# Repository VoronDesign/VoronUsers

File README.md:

# VoronUsers user mod repository

Welcome to VoronUsers. This is a place to share your mods for the VoronDesign 3D printers and find useful mods and resources from other Voron community members.

Check the [`printer_mods`](./printer_mods) folder for mods that apply to the current generation of printers. 

All mods that apply to older (=legacy) printers can be found in the [`legacy printers`](./legacy_printers) folder.

Mods where the authors have abandoned development can be found in the [`orphaned mods`](./orphaned_mods/) folder. If you want to start maintaining one of them, feel free to reach out via a [GitHub issue](https://github.com/VoronDesign/VoronUsers/issues/new/choose).

Looking to submit a mod? Check the [mod submission rules](https://github.com/VoronDesign/VoronUsers/wiki/Mod-Submission-Rules) and instructions on [how to submit to VoronUsers](https://github.com/VoronDesign/VoronUsers/wiki/How-to-Submit-to-VoronUsers)

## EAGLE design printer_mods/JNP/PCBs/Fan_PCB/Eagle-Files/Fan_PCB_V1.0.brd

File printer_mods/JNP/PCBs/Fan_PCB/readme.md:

Notes can be found in the schematic

Standard 2 layer PCB, 35µm (1oz) copper, TG-135, 1.6mm thickness, surface finish of your choice

Dimensions: 40x30mm

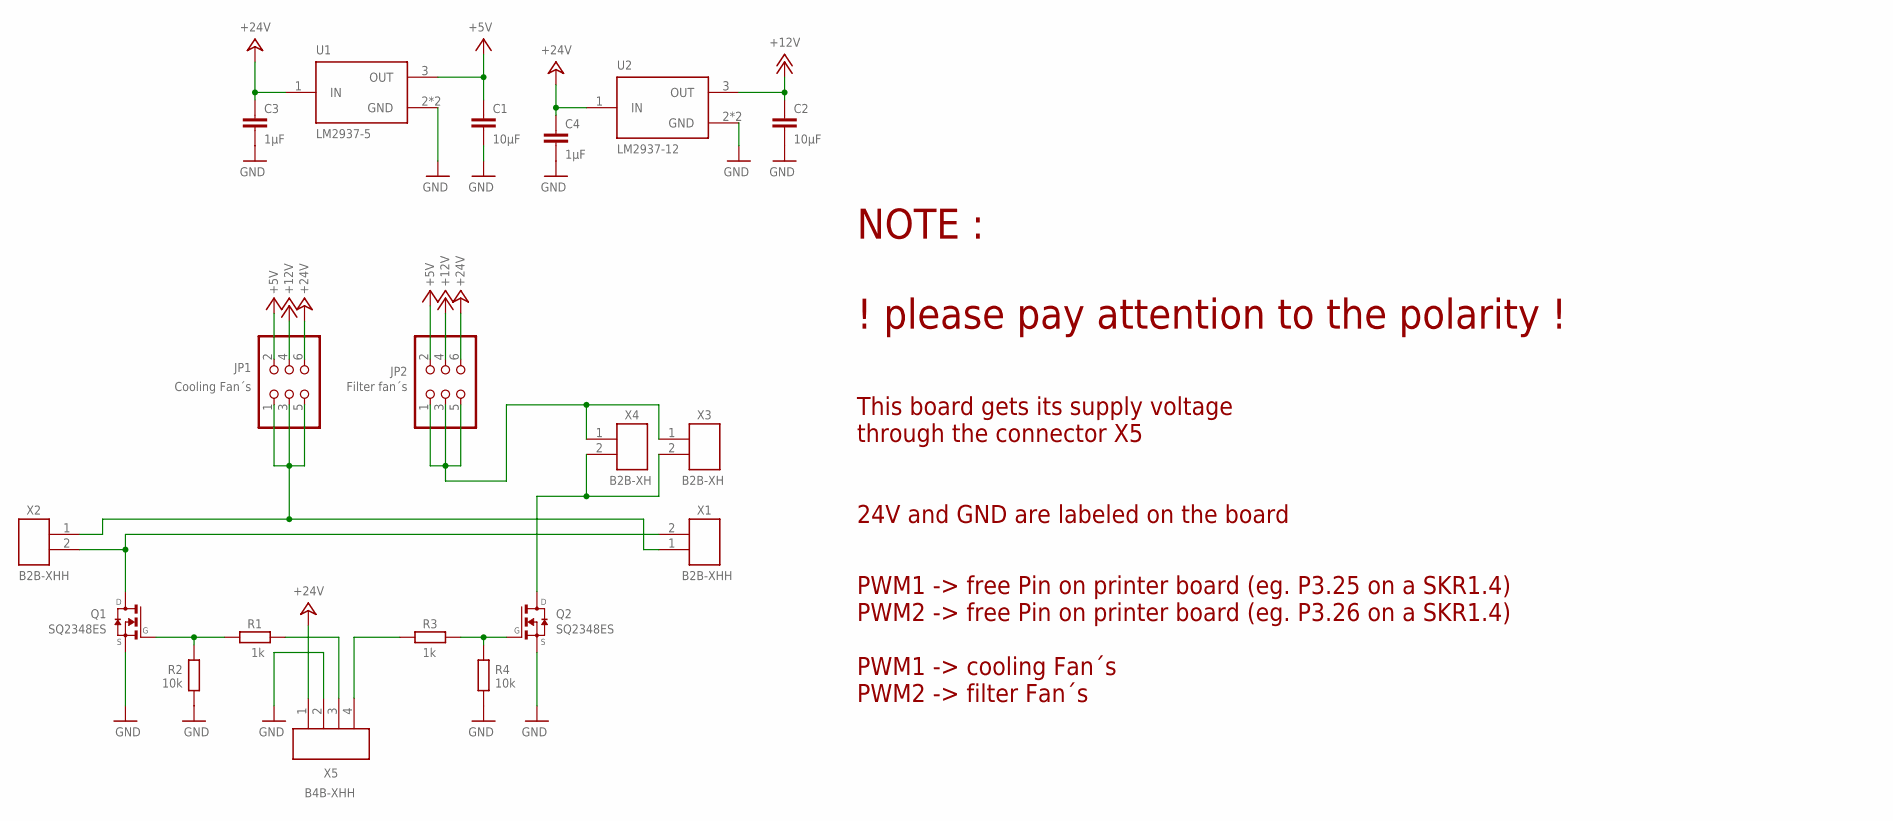
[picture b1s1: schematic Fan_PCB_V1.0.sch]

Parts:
C1, C2: 10µF; C1206
C3, C4: 1µF; C1206
JP1: Cooling Fan´s; 2X03
JP2: Filter fan´s; 2X03
Q1, Q2: SQ2348ES; TRANSISTOR-FET_SOT23
R1, R3: 1k; R0805
R2, R4: 10k; R0805
U1: LM2937-5; SOT-223-4
U2: LM2937-12; SOT-223-4
X1, X2: B2B-XHH; B2B-XH-H
X3, X4: B2B-XH; B2B-XH-A
X5: B4B-XHH; B4B-XH-H

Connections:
+5V: C1.1, JP1.2, JP2.2, U1.3 (OUT)
+12V: C2.1, JP1.4, JP2.4, U2.3 (OUT)
+24V: C3.1, C4.1, JP1.6, JP2.6, U1.1 (IN), U2.1 (IN), X5.1
GND: C1.2, C2.2, C3.2, C4.2, Q1.2 (S), Q2.2 (S), R2.1, R4.1, U1.2 (GND), U1.4 (GND), U2.2 (GND), U2.4 (GND), X5.2
unnamed: Q1.3 (D), X1.2, X2.2
unnamed: JP1.1, JP1.3, JP1.5, X1.1, X2.1
unnamed: Q2.3 (D), X3.2, X4.2
unnamed: JP2.1, JP2.3, JP2.5, X3.1, X4.1
unnamed: Q1.1 (G), R1.2, R2.2
unnamed: Q2.1 (G), R3.2, R4.2
unnamed: R1.1, X5.3
unnamed: R3.1, X5.4

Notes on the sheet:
PWM1 -> free Pin on printer board (eg. P3.25 on a SKR1.4) PWM2 -> free Pin on printer board (eg. P3.26 on a SKR1.4) PWM1 -> cooling Fan´s PWM2 -> filter Fan´s
This board gets its supply voltage through the connector X5 24V and GND are labeled on the board
NOTE : ! please pay attention to the polarity !

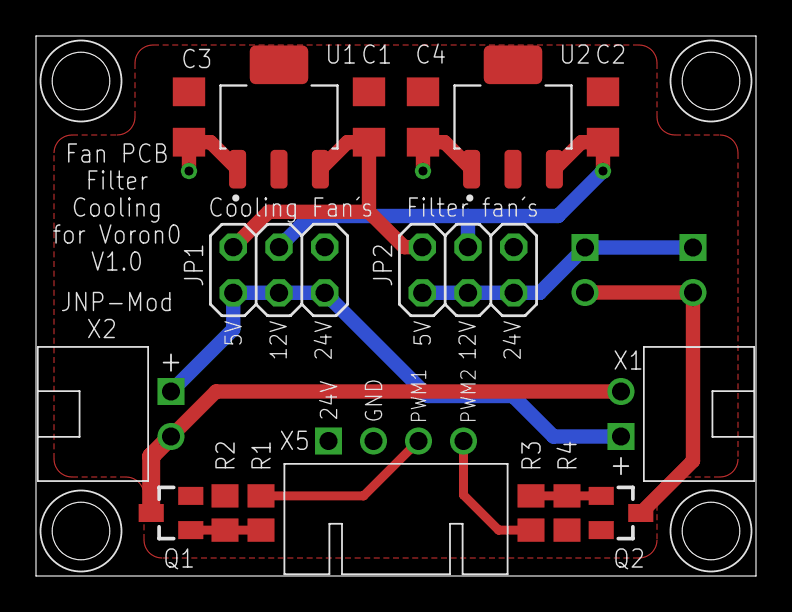
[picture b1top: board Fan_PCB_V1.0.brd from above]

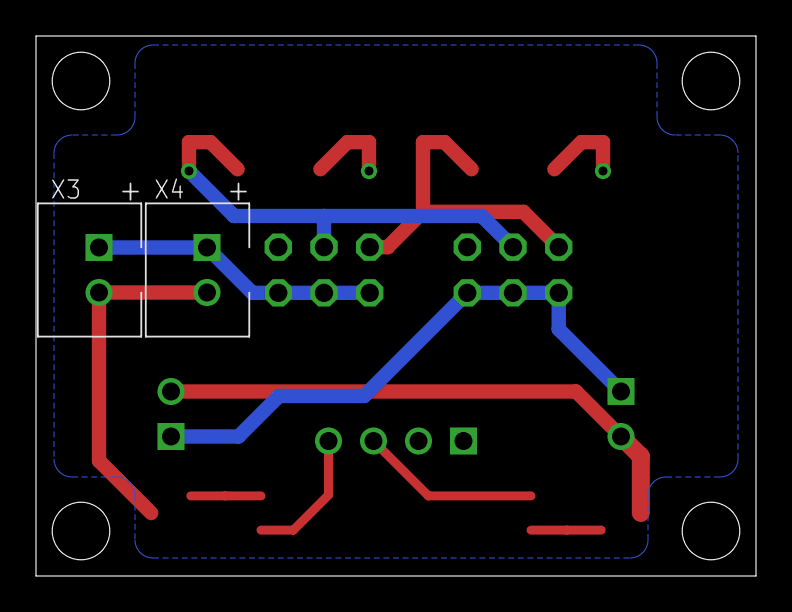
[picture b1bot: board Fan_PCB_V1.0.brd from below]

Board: 2 copper layers, 40.0 x 30.0 mm, 19 parts (2 on the bottom side), 12 nets.

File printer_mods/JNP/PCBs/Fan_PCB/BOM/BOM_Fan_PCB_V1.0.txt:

Qty Value         Device                  Package              Parts  Description                    
2   10k           RESISTOR			      0805                 R2, R4 RESISTOR    
2   10µF          CAPACITOR               1206                 C1, C2 CAPACITOR    
2   1k            RESISTOR				  0805                 R1, R3 RESISTOR  
2   1µF           CAPACITOR               1206                 C3, C4 CAPACITOR     
2   B2B-XH        JST-XH                  B2B-XH-A             X3, X4 JST XH 2Pin Header                               
2   B2B-XHH       JST-XH                  B2B-XH-H             X1, X2 JST XH 2Pin Header 90° Angle                              
1   B4B-XHH       JST-XH                  B4B-XH-H             X5     JST XH 4Pin Header 90° Angle                              
1   Cooling Fan´s PINHD-2X3               2X03                 JP1    PIN HEADER                     
1   Filter fan´s  PINHD-2X3               2X03                 JP2    PIN HEADER                     
1   LM2937-12     TPS7B6933QDCYRQ1        SOT-223-4            U2     IC REG LIN SOT223-4 
1   LM2937-5      TPS7B6933QDCYRQ1        SOT-223-4            U1     IC REG LIN SOT223-4 
2   SQ2348ES      TRANSISTOR-FET_DMN2004K TRANSISTOR-FET_SOT23 Q1, Q2 N-Channel Enhancement MOSFET

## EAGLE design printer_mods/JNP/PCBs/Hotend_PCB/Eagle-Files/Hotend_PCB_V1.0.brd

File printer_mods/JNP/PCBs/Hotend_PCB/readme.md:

Notes can be found in the schematic

Standard 4 layer PCB, 35µm (1oz) copper, TG-135, 1.6mm thickness, surface finish of your choice

Dimensions: 54x33.5mm

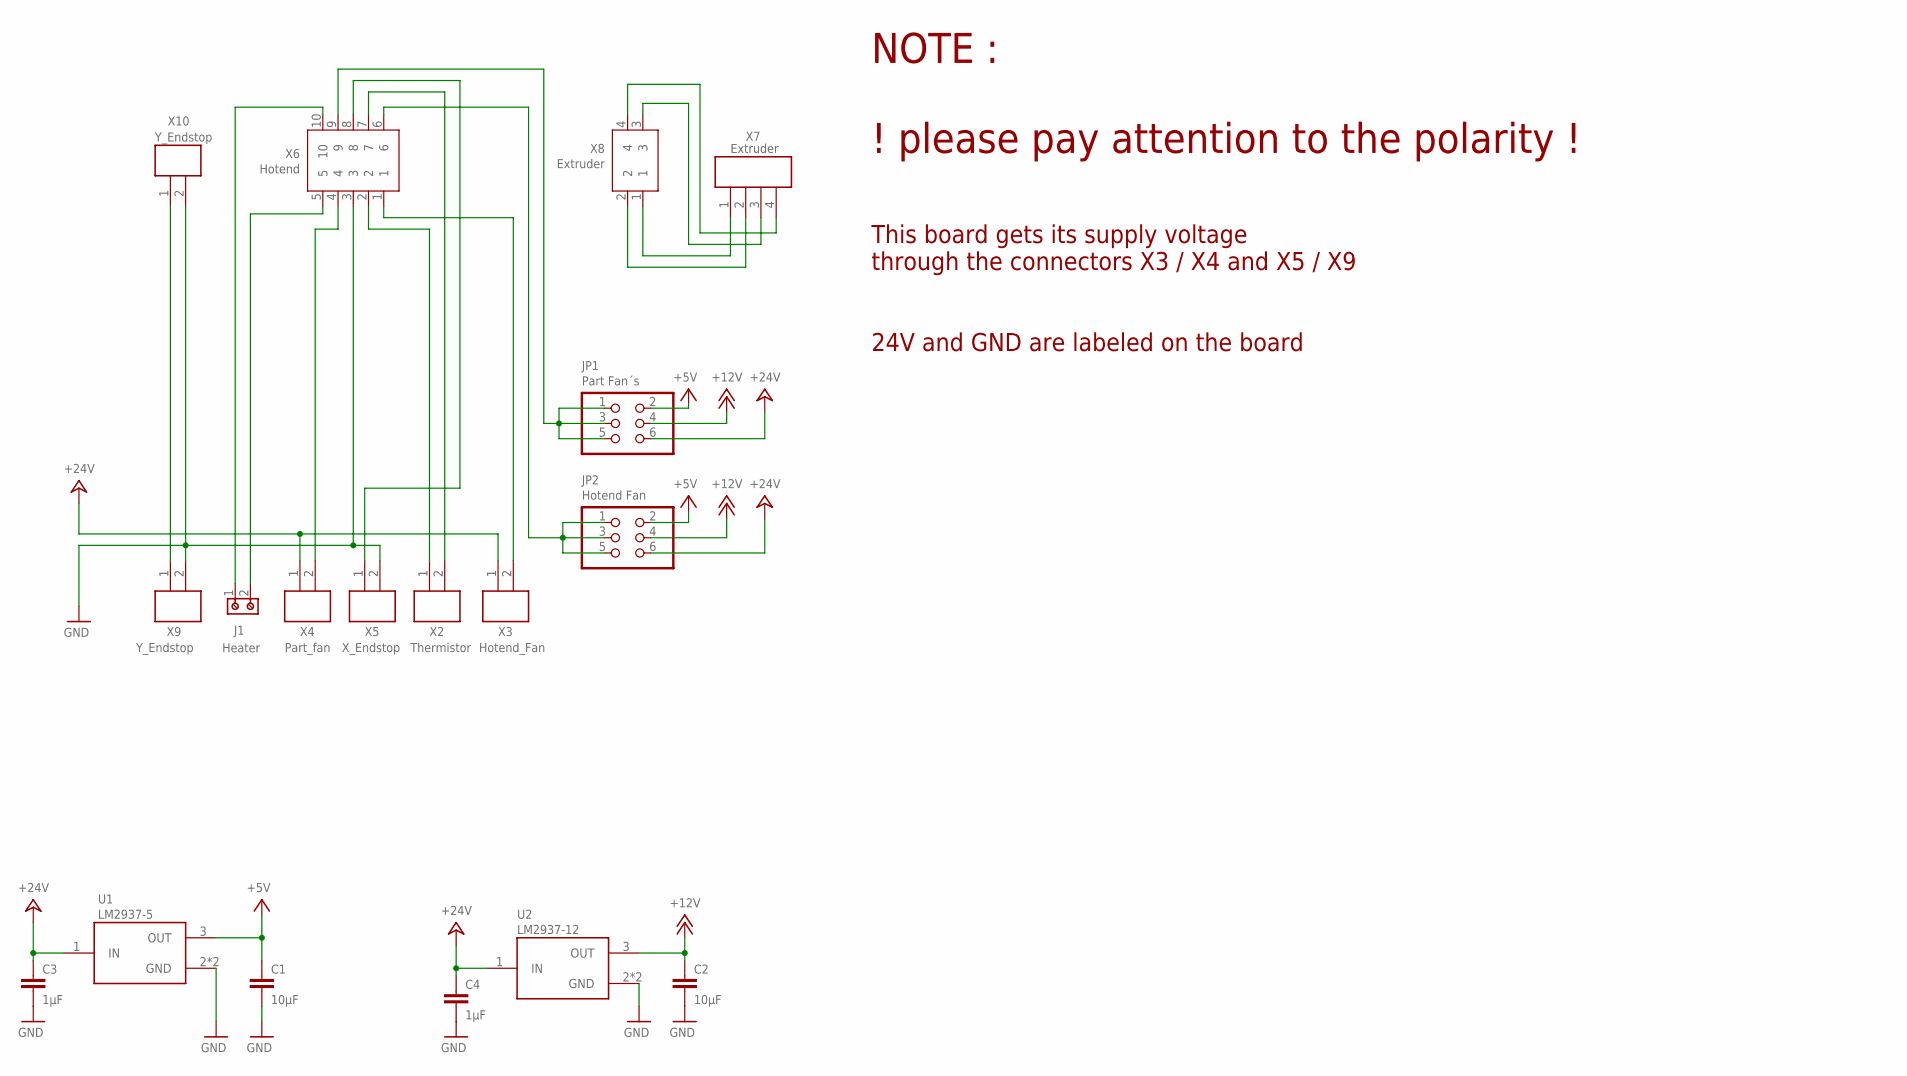
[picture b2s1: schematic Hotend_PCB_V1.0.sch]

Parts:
C1, C2: 10µF; C1206
C3, C4: 1µF; C1206
J1: Heater; 691101710002
JP1: Part Fan´s; 2X03
JP2: Hotend Fan; 2X03
U1: LM2937-5; SOT-223-4
U2: LM2937-12; SOT-223-4
X2: Thermistor; B2B-XH-H
X3: Hotend_Fan; B2B-XH-H
X4: Part_fan; B2B-XH-H
X5: X_Endstop; B2B-XH-H
X6: Hotend; 105314-1310
X7: Extruder; B4B-XH-A
X8: Extruder; 105314-1304
X9, X10: Y_Endstop; B2B-XH-H

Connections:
+5V: C1.1, JP1.2, JP2.2, U1.3 (OUT)
+12V: C2.1, JP1.4, JP2.4, U2.3 (OUT)
+24V: C3.1, C4.1, JP1.6, JP2.6, U1.1 (IN), U2.1 (IN), X3.1, X4.1
GND: C1.2, C2.2, C3.2, C4.2, U1.2 (GND), U1.4 (GND), U2.2 (GND), U2.4 (GND), X5.2, X6.3, X9.2, X10.2
unnamed: X7.4, X8.4
unnamed: X7.3, X8.3
unnamed: X7.1, X8.1
unnamed: X7.2, X8.2
unnamed: JP1.1, JP1.3, JP1.5, X6.9
unnamed: JP2.1, JP2.3, JP2.5, X6.6
unnamed: J1.1, X6.10
unnamed: J1.2, X6.5
unnamed: X5.1, X6.8
unnamed: X2.1, X6.2
unnamed: X2.2, X6.7
unnamed: X3.2, X6.1
unnamed: X4.2, X6.4
unnamed: X9.1, X10.1

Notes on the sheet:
This board gets its supply voltage through the connectors X3 / X4 and X5 / X9 24V and GND are labeled on the board
NOTE : ! please pay attention to the polarity !

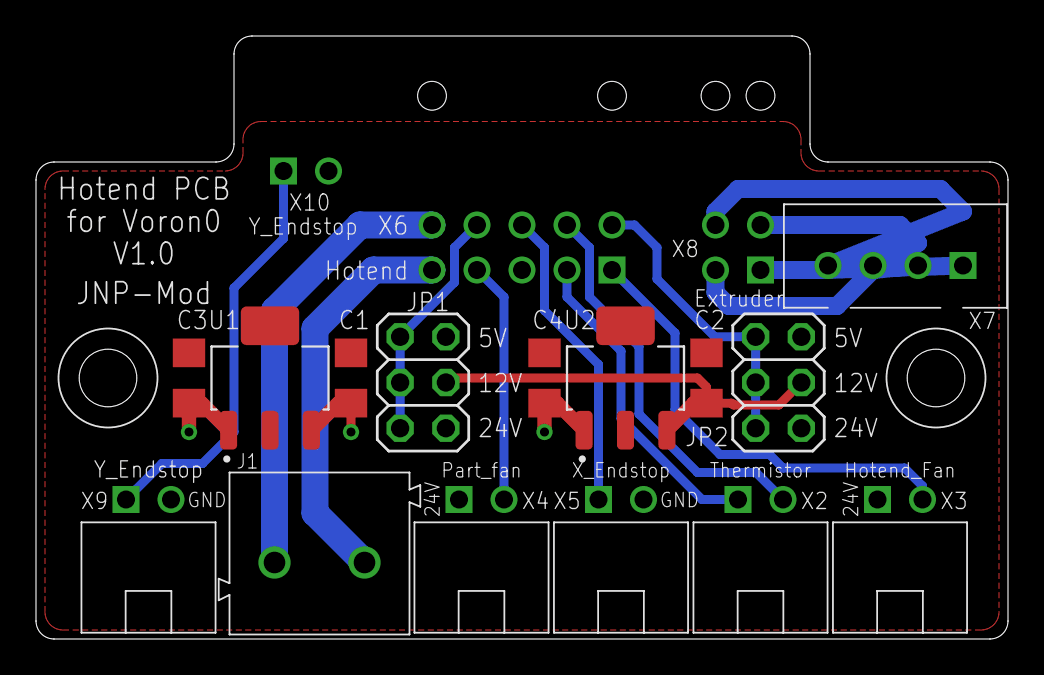
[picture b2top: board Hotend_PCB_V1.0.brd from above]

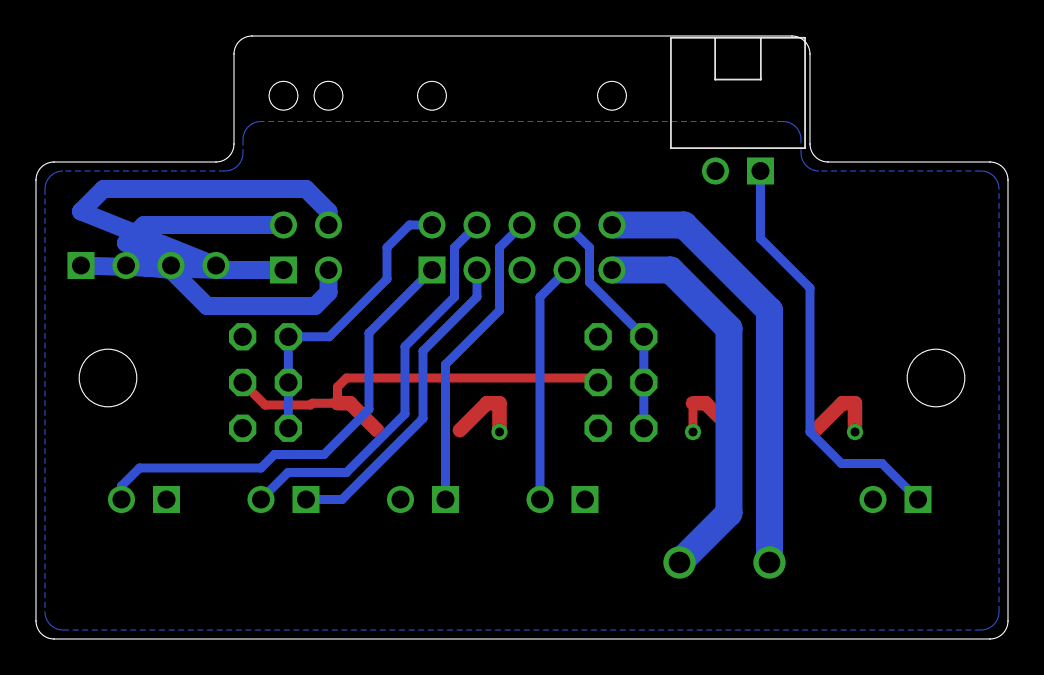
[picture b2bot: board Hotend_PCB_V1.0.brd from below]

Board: 4 copper layers, 54.0 x 33.5 mm, 18 parts (3 on the bottom side), 18 nets.

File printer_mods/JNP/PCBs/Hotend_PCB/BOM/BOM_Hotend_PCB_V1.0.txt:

Qty Value      Device           Package or Vendor-Nr.		Parts   Description                                     
2   10µF       CAPACITOR        1206         				C1, C2  CAPACITOR                      
2   1µF        CAPACITOR        1206         				C3, C4  CAPACITOR                      
1   Extruder   JST-XH           B4B-XH-A     				X7      JST XH 4Pin Header                                                
1   Extruder   NANOFIT_4PIN     105314-1304  				X8      Molex NanoFit                                                
1   Heater     Terminal Block   691101710002 				J1      Wuerth WR-TBL Serie 101 - 5.00 mm Horiz. Entry Modular 
1   Hotend     NANOFIT_10PIN90  105314-1310  				X6      Molex NanoFit                                                
1   Hotend Fan PINHD-2X3        2X03         				JP2     PIN HEADER                                      
1   Hotend_Fan JST-XH           B2B-XH-H     				X3      JST XH 2Pin Header 90° Angle                                               
1   LM2937-12  TPS7B6933QDCYRQ1 SOT-223-4    				U2      IC REG LIN SOT223-4                  
1   LM2937-5   TPS7B6933QDCYRQ1 SOT-223-4    				U1      IC REG LIN SOT223-4                  
1   Part Fan´s PINHD-2X3        2X03         				JP1     PIN HEADER                                      
1   Part_fan   JST-XH           B2B-XH-H     				X4      JST XH 2Pin Header 90° Angle                                                
1   Thermistor JST-XH           B2B-XH-H     				X2      JST XH 2Pin Header 90° Angle                                                
1   X_Endstop  JST-XH           B2B-XH-H     				X5      JST XH 2Pin Header 90° Angle                                                
2   Y_Endstop  JST-XH           B2B-XH-H     				X9, X10 JST XH 2Pin Header 90° Angle

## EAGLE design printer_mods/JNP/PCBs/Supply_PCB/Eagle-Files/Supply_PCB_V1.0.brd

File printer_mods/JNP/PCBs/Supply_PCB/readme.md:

Notes can be found in the schematic

Standard 4 layer PCB, 35µm (1oz) copper, TG-135, 1.6mm thickness, surface finish of your choice

Dimensions: 82.5x22mm

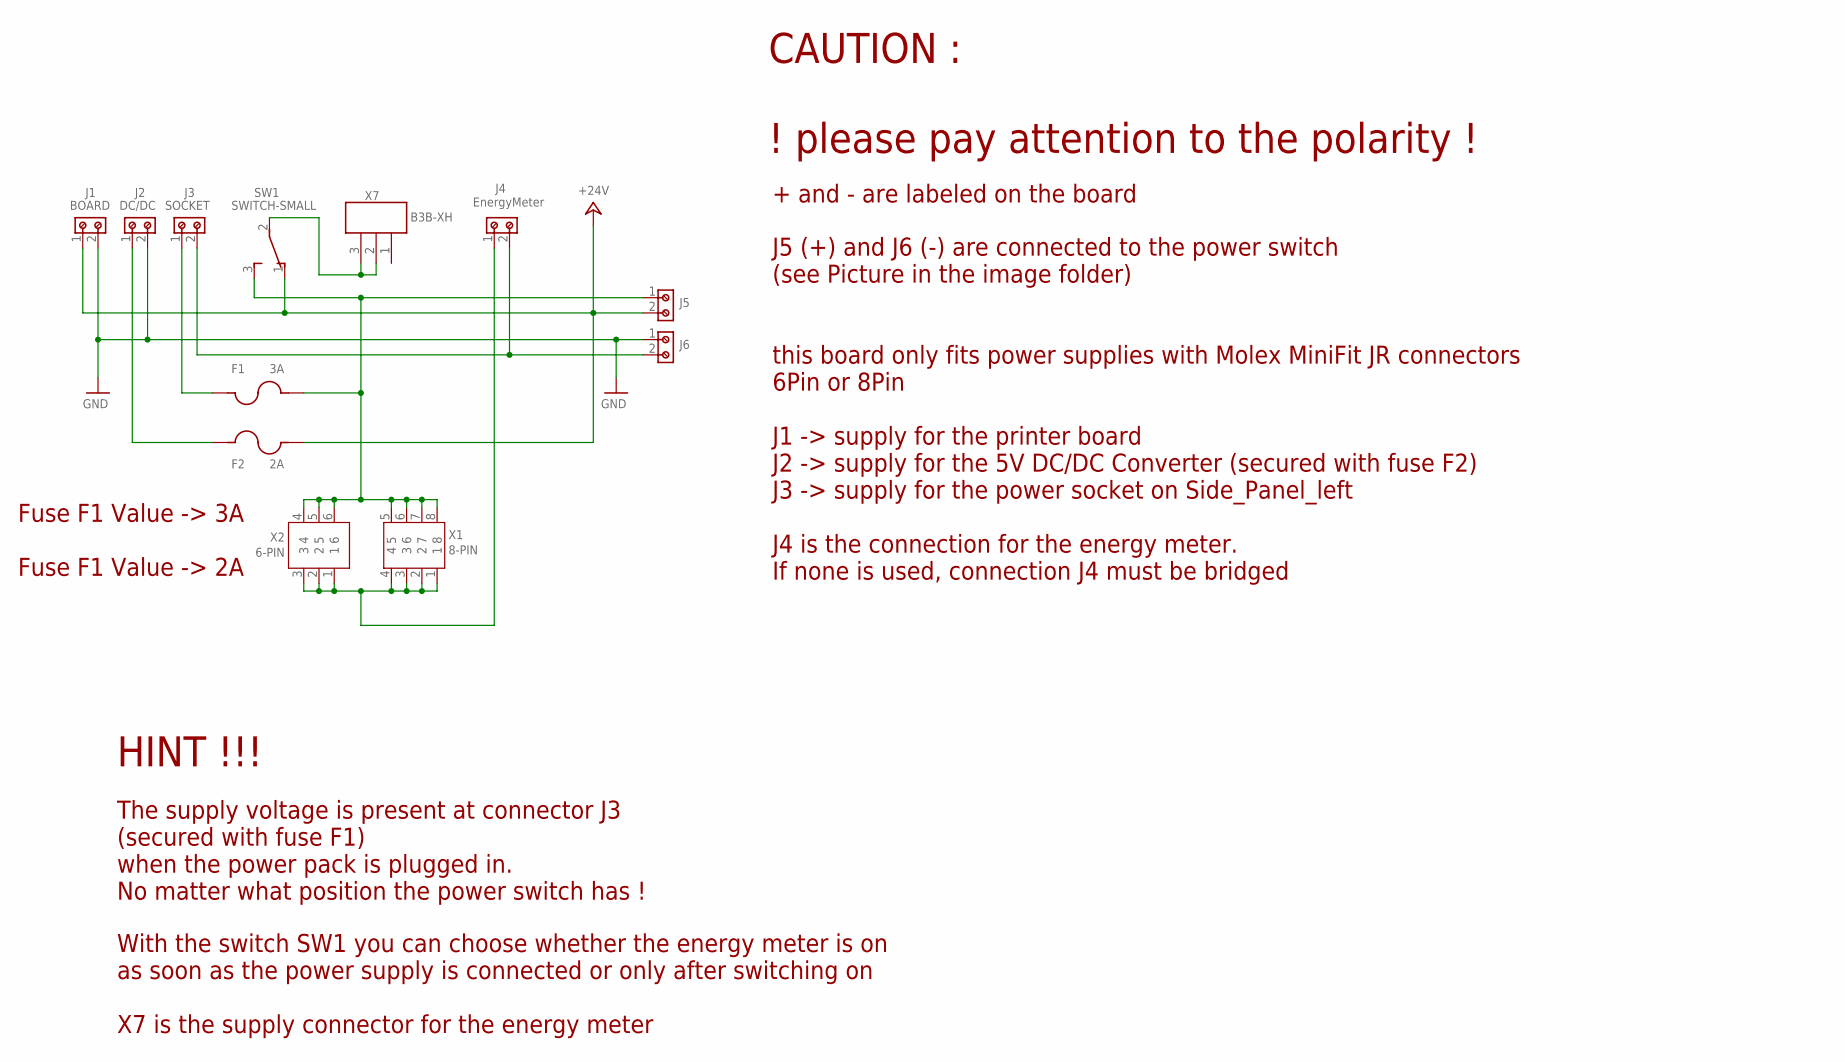
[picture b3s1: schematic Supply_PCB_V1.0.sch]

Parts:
F1: 3A; H7810
F2: 2A; H7810
J1: BOARD; 691101710002
J2: DC/DC; 691101710002
J3: SOCKET; 691101710002
J4: EnergyMeter; 691101710002
J5, J6: 691101710002
SW1: SWITCH-SMALL; V_SWITCH
X1: 8-PIN; 172447-0208
X2: 6-PIN; 172447-1206
X7: B3B-XH; B3B-XH-A

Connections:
+24V: F2.2, J1.1, J5.2, SW1.1 (O)
GND: J1.2, J2.2, J6.1
unnamed: F1.2, J3.1
unnamed: F2.1, J2.1
unnamed: J4.1, X1.1, X1.2, X1.3, X1.4, X2.1, X2.2, X2.3
unnamed: J3.2, J4.2, J6.2
unnamed: F1.1, J5.1, SW1.3 (S), X1.5, X1.6, X1.7, X1.8, X2.4, X2.5, X2.6
unnamed: SW1.2, X7.2, X7.3

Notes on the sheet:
+ and - are labeled on the board
CAUTION : ! please pay attention to the polarity !
J5 (+) and J6 (-) are connected to the power switch (see Picture in the image folder) this board only fits power supplies with Molex MiniFit JR connectors 6Pin or 8Pin J1 -> supply for the printer board J2 -> supply for the 5V DC/DC Converter (secured with fuse F2) J3 -> supply for the power socket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
HINT !!!
The supply voltage is present at connector J3 (secured with fuse F1) when the power pack is plugged in. No matter what position the power switch has !
With the switch SW1 you can choose whether the energy meter is on as soon as the power supply is connected or only after switching on X7 is the supply connector for the energy meter
Fuse F1 Value -> 3A Fuse F1 Value -> 2A

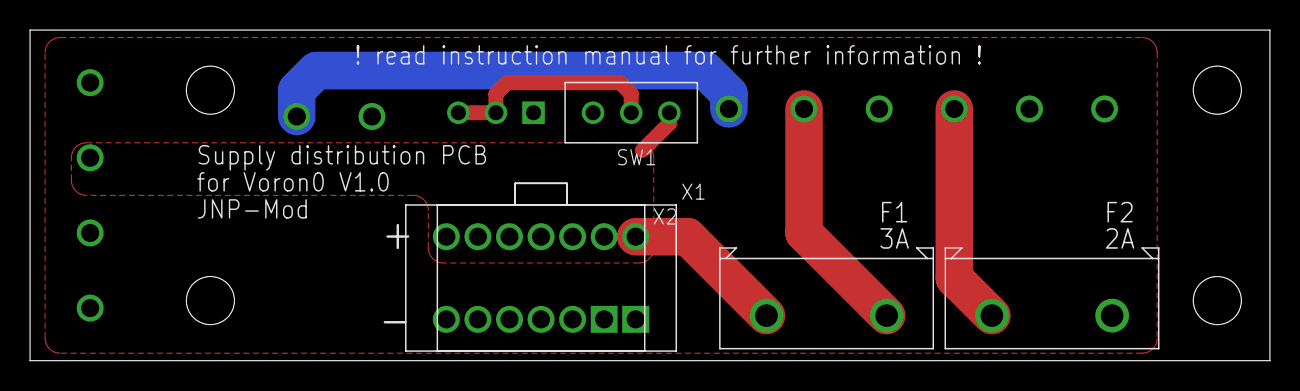
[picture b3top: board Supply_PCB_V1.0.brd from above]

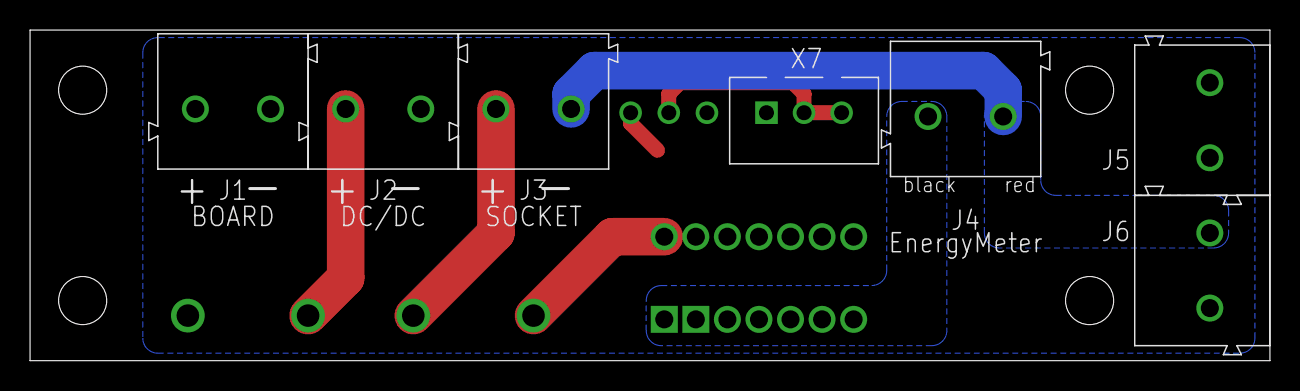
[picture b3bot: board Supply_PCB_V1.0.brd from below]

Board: 4 copper layers, 82.5 x 22.0 mm, 12 parts (7 on the bottom side), 8 nets.

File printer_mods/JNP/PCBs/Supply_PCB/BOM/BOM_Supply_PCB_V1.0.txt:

Qty Value        Device         	Package or Vendor-Nr.   Parts	Description                                     
2   to Switch    Terminal Block 	691101710002 			J5, J6	Wuerth WR-TBL Serie 101 - 5.00 mm Horiz. Entry Modular 
1   2A           01530008ZIMAXX 	H7810        			F2		FUSE HOLDER BLADE 32V 15A PCB                   
1   3A           01530008ZIMAXX 	H7810        			F1		FUSE HOLDER BLADE 32V 15A PCB                   
1   6-PIN        6-PIN          	172447-0206  			X2		Molex MiniFit JR                                                
1   8-PIN        8-PIN          	172447-0208  			X1		Molex MiniFit JR                                                
1   B3B-XH       JST-XH         	B3B-XH-A     			X7		JST XH 3Pin Header                                                
1   BOARD        Terminal Block 	691101710002 			J1		Wuerth WR-TBL Serie 101 - 5.00 mm Horiz. Entry Modular 
1   DC/DC        Terminal Block 	691101710002 			J2		Wuerth WR-TBL Serie 101 - 5.00 mm Horiz. Entry Modular 
1   EnergyMeter  Terminal Block 	691101710002 			J4		Wuerth WR-TBL Serie 101 - 5.00 mm Horiz. Entry Modular 
1   SOCKET       Terminal Block 	691101710002 			J3		Wuerth WR-TBL Serie 101 - 5.00 mm Horiz. Entry Modular 
1   SWITCH-SMALL SWITCH-SMALL   	V_SWITCH     			SW1		Switch (Amazon B00O9YPJKY) or Pinheader for Jumper                                                
1   Powerswitch  JWM21RA2A			SWITCH		 			SW2		NKK Rocker Switches 10A DPST

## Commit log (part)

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2023-12-25 Remove label check from pull_request_ci.yml
2023-12-25 initial add
2023-12-25 Minor updates to follow submissions rules
2023-12-25 Update README.md
    updated to relative images
2023-12-25 replacing STEP file with chamfers
2023-12-25 Delete printer_mods/dankeeling/CreativeLiveCameraMount/Images/20231224_211032~2.jpg
    Replacing with underscore
2023-12-25 Update .metadata.yml
    Cleaning up filenames
2023-12-25 Update README.md
    cleanup of URL
2023-12-25 Create Folder
2023-12-26 Update README.md
    changed video link to link to youtube
2023-12-26 Update README.md
    Updated YouTube link description
2023-12-26 Toolhead for Phaetus Dragon UHF/UHF mini (#1013)
2023-12-26 Generate VoronUsers README
    [skip ci]
2023-12-27 V0 Electronics Bay Modesty Mesh (#1014)
2023-12-27 Add Umbilical Collar
2023-12-27 Universal Phone mount by AVieira-1 (#1017)
    * Create metadata.yml
    * Create metadata.yml
    * Add files via upload
    * Delete printer_mods/AVieira/metadata.yml
    * Update README.md
    * Update README.md
2023-12-27 V0 Umbilical Collar by MapleLeafMakers (#1020)
2023-12-27 V0 Stealth Handles by MapleLeafMakers (#1019)
2023-12-27 Add V0 Upper Rear Bowden Inlet (URBI)
2023-12-28 Add 0.4mm bottom chamfer to all parts
2023-12-28 update compatibility in readme
2023-12-28 Add V0 Upper Rear Bowden Inlet (URBI) (#1021)
2023-12-28 Update modesty-mesh readme (#1022)
2023-12-29 Add Rainbow Serial Bumper for Trident
2023-12-29 add .metadata.yml
2023-12-29 remove unused thumbnail.png
2023-12-29 remove thumbnail.png from .metadata.yml
2023-12-29 Add Rainbow Serial Bumper for Trident (#1023)
2023-12-30 Backplates for Voron 2.4
2023-12-30 Structured
2023-12-30 Renamed structure
2023-12-30 Renamed the files and added STEP
2023-12-30 Placed the yml in the correct folder
2023-12-30 First upload
2023-12-30 Creative Live! Camera Mount by DanKeeling (#1018)
    * initial add
    * Update README.md
    * Minor updates to follow submissions rules
    * Add files via upload
    * Update README.md
    * Add files via upload
2023-12-30 fix typo in .metadata.yml
2023-12-30 add 0.4mm bottom chamfer to some carriers
2023-12-30 Matchstick Diffusers by MapleLeafMakers (#1025)
2023-12-31 Kirigami Stealth Bumper by MapleLeafMakers (#1028)
    * Add Kirigami Stealth Bumper
    * fix typo in .metadata.yml
    * add 0.4mm bottom chamfer to some carriers
2024-01-01 2.4 Bedfan Backplates by Ferdi360 (#1027)
    * First upload
    * Resolved requested changes
    * Update printer_mods/Ferdi360/2.4_Bedfan_Backplates/.metadata.yml
    * Update printer_mods/Ferdi360/2.4_Bedfan_Backplates/README.md
    ---------
2024-01-03 add sample mod
2024-01-04 remove render
2024-01-09 Re-generate VoronUsers README with latest changes
    [skip ci]
2024-01-09 add stls to metadata
2024-01-15 add VSW and VL to compatibility
2024-01-18 Update README.md and add new banner by @hartk1213
2024-01-18 Add issue template for mod adoption
    [skip ci]
2024-01-21 Fix mods without printer compatibility
2024-01-21 Flush mount for hdmi and usb c (#1)
    * Adds CAD and STL files for flush mount mod.
    * Renames mod folder name.
    * Updates dimensions of flush mount opening.
    * Adds photos and updates `README.md`.
2024-01-22 Adds image for BATIGE Mount.
2024-01-23 Removes possibly copyright image and updates `metadata.yml`.
2024-01-23 Updates `README.md` to no longer use `html`.
2024-01-23 Adds `All_Sizes_2` in `README.md`.
2024-01-25 Flush mount for hdmi and usb c by ppak10 (#1031)
    * Flush mount for hdmi and usb c (#1)
    * Adds CAD and STL files for flush mount mod.
    * Renames mod folder name.
    * Updates dimensions of flush mount opening.
    * Adds photos and updates `README.md`.
    * Reduces `.stl` size, adds `0.4 mm` chamfer, and notes installation.
2024-02-01 5160T Plus Mounts, LRS DIN Mount Offset and Lever Connector Mount Side Fan Support by Dr-Info (#1033)
    * Create README.md
    * Create mounts_btt_5160t_plus.step
    * Add files via upload
    * Create 30mm_fan_shroud_5160T_plus_x2.stl
    * Add files via upload
    * Create 1515_bracket_5160T_plus.stl
2024-02-18 Mod Adoption: Dr-Info adopts V2.4 Z drive tensioner from edwardyeeks
2024-02-22 Mod for the skirts to resolve collision
    Skirts are interfering with the screen mount. Let's cut the skirt
2024-02-22 Added 300 and 350mm skirts mod
    Cut the bit from skirts to resolve the interference with screen frame
2024-02-22 Added the full assembly reference and an update to readme
    Added the note about non-standard skirts requirement
2024-02-23 Mod Adoption: Dr-Info adopts V2.4 Z drive tensioner from edwardyeeks (#1034)
2024-02-29 Add CAD Files for most xbst mods
2024-02-29 whitespace cleanup
2024-02-29 fix cad listing in .metadata.yml
2024-03-09 2020 aplic cam mount
2024-03-09 moved to subfolder
2024-03-09 deleted duplicates
2024-03-09 fixed typos
2024-03-10 renamed metadata.yml, added shortened version, removed stl import
2024-03-10 fixed PR issues
2024-03-10 corrected typos/quantities in BOM
2024-03-14 Add CAD Files for most xbst mods (#1036)
    * Add CAD Files for most xbst mods
    * whitespace cleanup
    * fix cad listing in .metadata.yml
2024-03-14 2020 aplic cam mount by techprolet (#1039)
    * 2020 aplic cam mount
    * renamed metadata.yml, added shortened version, removed stl import
    * fixed PR issues
    * corrected typos/quantities in BOM
    * fixed typose, added M3 spacer length
    ---------
2024-03-14 add CAD for khay mods (#1037)
2024-03-25 feat: add switchwire cyd screen case files
2024-03-26 fix: change orientation for best print
2024-03-27 fix: add bridging to counterbored holes
2024-03-31 add switchwire cyd screen case files by Reemuson (#1041)
    * feat: add switchwire cyd screen case files
    * docs: added gif to README
    * fix: change orientation for best print
    * fix: add bridging to counterbored holes
2024-04-28 Create README.md
    Initial page for mod variation
2024-04-28 Create README.md
    Create page for mod variation
2024-04-28 Create README.md
    added page for mod
2024-05-02 moving readme.md file in the correct folder
2024-05-07 Adds CAD, STL, and Images.
2024-05-07 Adds images and description to files.
2024-05-07 Updates `.metadata.yml` with correct `.STL` file links and fixes stls.
2024-05-09 Update README.MD
    Removed Paypal link
2024-05-12 corrected the errors
    - shrieked the file size
    - corrected corrupted files
    - updated yml file
    - added Rapido UHF
2024-05-12 Shorter description
2024-05-13 assembley pictures
2024-05-13 assembly.md
2024-05-13 updated assembly.md
2024-05-13 assembley.md
    adding guide how to assemble the toolhead
2024-05-13 updated style
2024-05-13 updated image style
2024-05-13 Update v6_heatsink_mod.md
    Grammar
2024-05-13 Update toolhead_assembly.md
    explained the steps
2024-05-15 Update metadata.yml & added readme
2024-05-16 Upload STL and CAD. Update metadata.yml
2024-05-16 Update STLs orientation
2024-05-16 Added images and completed the README.md
2024-05-16 Add alt text to images
2024-05-16 Fixed image path typo in metadata.yml. Removed f3z file, lighten the step file removing unecessary components.
2024-05-18 Add gallery images to metadata.yml file
2024-05-19 Change name Extruder to Extrusion
2024-05-20 left STL to Binary
2024-05-22 yml updated
2024-05-22 removed the 7z archive
2024-05-23 Create a new directory
2024-05-23 Removed old directory
2024-06-04 initial
2024-06-06 fixed linting errors
2024-06-17 fixed image links in metadata
2024-06-19 Ballpoint pen spring DIN clips assortment by aeresov (#1048)
    * initial
    * fixed linting errors
    * fixed image links in metadata
2024-07-02 WAGO_221-415_mount_3x5_M3_fasteners
    And here's the second one I'd like to submit.
2024-07-02 removed separate mod
    removed another mod I want to submit.
2024-07-02 WAGO_221-415_mount_3x5_M3_fasteners
    This is a reworked WAGO mount using M3 fasteners instead of M5, it is also a bit thinner so it fits between DIN rails easier.
2024-07-02 Changes
    Changed discord_username
2024-07-02 Corrected?
    I removed an empty line in the description that was used to space the sentences, maybe that fixed it?
2024-07-02 Punctuation correction
    Forgot to add a space after a period in description, corrected.
2024-07-02 pre-emptive correction
    removed an empty line for spacing sentences in description.
2024-07-02 Shortened Description
    Shortened description per advice on other mod submission.
2024-07-04 Rs 50 5 bracket by Rikers-Beard (#1050)
    * RS-50-5 Bracket
    This is my first attempt at submitting a mod, sorry if I messed anything up!
    * WAGO_221-415_mount_3x5_M3_fasteners
    And here's the second one I'd like to submit.
    * removed separate mod
    removed another mod I want to submit.
2024-07-12 Publish ‘Double_GEAR_ratio_Z’
2024-07-13 Add Assemble Instructions，Resize photo
2024-07-14 edit read me and YAML file
2024-07-14 fix Voron LOGO for stl， change description in readme
2024-07-14 Double_GEAR_ratio_Z by zzp8202 (#1052)
    * Publish ‘Double_GEAR_ratio_Z’
    * add photo
    * Add Assemble Instructions，Resize photo
    * Update Z_Belt_Clamp_Upper_x8.STL
    * edit read me and YAML file
    * fix Voron LOGO for stl， change description in readme
2024-09-22 Orientation for printing
2024-09-22 New mod : PEI Stop
2024-09-24 PEI Stop by Itzo1978 (#1055)
2024-10-03 use native Jinja variable _bucket_pos
    The previous implementation of dynamically changing bucket_pos on each
    run had an extremely confusing semantic of changing the variable early
    in the execution of the macro but see the effect only on the next run of
    the macro. This led to the situation that the first bucket position
    after the machine started was never selected randomly, only all later
    ones. While this for sure is not a major problem of the implementation
2024-10-03 variable_bucket_park: select bucket to park nozzle after cleaning
    The previous implementation always parked the nozzle over the left
    bucket after cleaning. While this makes sense in most cases it is
    problematic when you happen to have something installed over the left
    bucket, like the Klicky Probe. If parking the nozzle over the Klicky
    Probe there is a certain risk to pull it out of the docking station by
    accident with the move command following the cleaning procedure. When
2024-10-03 variable_bucket_purge: select bucket for purging
    In the original implementation, the bucket for purging was selected
    randomly. Since I wanted to park the nozzle always over the right
    bucket to avoid conflicts with the Klicky Probe and as such always
    oozing into that (on my 350 build) smaller right bucket I thought that
    it might be useful to compensate for this by always purging to the
    larger left bucket.
2024-10-06 Update orphaned_mods/edwardyeeks/Decontaminator_Purge_Bucket_&_Nozzle_Scrubber/Macros/ by schiele (#1057)
    * use native Jinja variable _bucket_pos
    The previous implementation of dynamically changing bucket_pos on each
    run had an extremely confusing semantic of changing the variable early
    in the execution of the macro but see the effect only on the next run of
    the macro. This led to the situation that the first bucket position
    after the machine started was never selected randomly, only all later
2024-10-14 Actually corrected the issues this time.
    I had STLs instead of STL and images instead of Images. Hopefully that's all it was!
2024-11-28 Update nozzlewiper.cfg - Wait for servo move before turning off
    The servo was turned off before it reached target angle.
2024-12-01 Updated as requested
    updated file names and formatting.
2024-12-02 Fix metadata.yml, add updated CAD files, update readme
2024-12-02 Remove M4P from step file, reorient parts for printing
2024-12-02 Add bom and instructions to README, update metadata
2024-12-09 New modded printhead v1
    pictures, stl, etc.
2025-03-29 v0 Foldable Display Mount
2025-03-29 Remove two unnecessary lines from the template that were mistakenly left in.
    Thanks to mjonuschat for spotting this.
2025-03-29 Update the README.
2025-04-05 Gantry And Wire Friendly Flush Extrusion Cover
    Gantry And Wire Friendly Flush Extrusion Cover UserMod submitted
2025-05-09 Added an ethernet adapter.
2025-05-28 Update README.md
    use new auto install script
2025-05-29 Update README.md (#1068)
    use new auto install script
2025-06-21 Rename 20250621_143212494[1].JPG to pic.JPG
2025-06-21 Rename pic.JPG to pic.jpg

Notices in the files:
parts and their libraries:
Wurth_Connectors_WR-TBL Wire Protector: Copyright: Würth Elektronik
